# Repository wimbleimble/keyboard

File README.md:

# keebydeeby

I'm sorry I couldn't think of a better name.

Pretty simple, TKL, ISO keyboard with RGB backlighting. Based around an
ATMega32u4, compatible with QMK (and probably a lot more).

## Repo Structure

```
├──📁 enclosure                - Enclosure CAD files.
├──📁 kicad                    - Schematic/PCB CAD file.
│   ├─📁 Custom.pretty         - Custom KiCAD footprints.
│   ├─📁 media                 - Miscellaneous Media Dependencies for PCB.
│   ├─📄 Custom.kicad_sym      - Custom KiCAD symbols.
│   ├─📄 keyboard.kicad_pro    - KiCAD project file.
│   ├─📄 keyboard.kicad_pcb    - PCB File
│   ├─📄 keyboard.kicad_sch    - Master schematic page.
│   ├─📄 key-matrix.kicad_sch  - Key matrix schematic page.
│   ├─📄 LEDS.kicad_sch        - RBG matrix schematic page.
│   ├─📄 mcu.kicad_sch         - Microcontroller schematic page.
│   ├─📄 fp-info-cache         - KiCAD internal file.
│   ├─📄 fp-lib-table          - KiCAD internal file
│   └─📄 sym-lib-table         - KiCAD internal file.
├─📁 plate                     - Plate CAD files.
│   └─📄 plate.svg             - CAD drawing of plate.
└─📄 README.md                 - You're looking at it.
```

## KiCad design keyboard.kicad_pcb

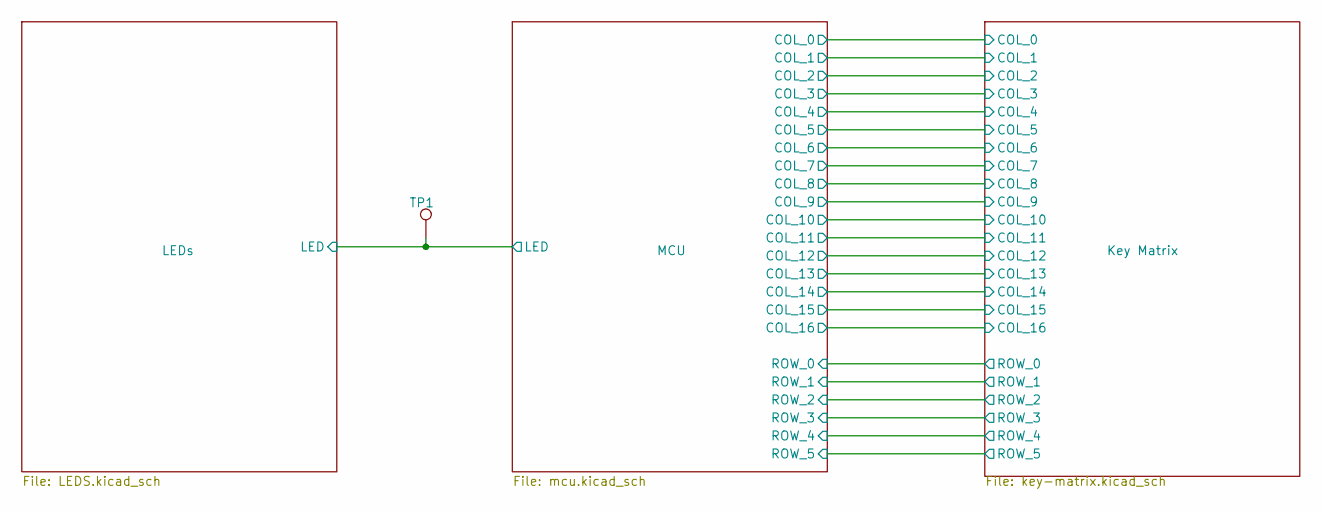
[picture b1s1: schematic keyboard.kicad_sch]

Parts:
TP1: TestPoint; TestPoint_THTPad_D1.0mm_Drill0.5mm

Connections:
/LEDs/LED: TP1.1; also elsewhere on the board

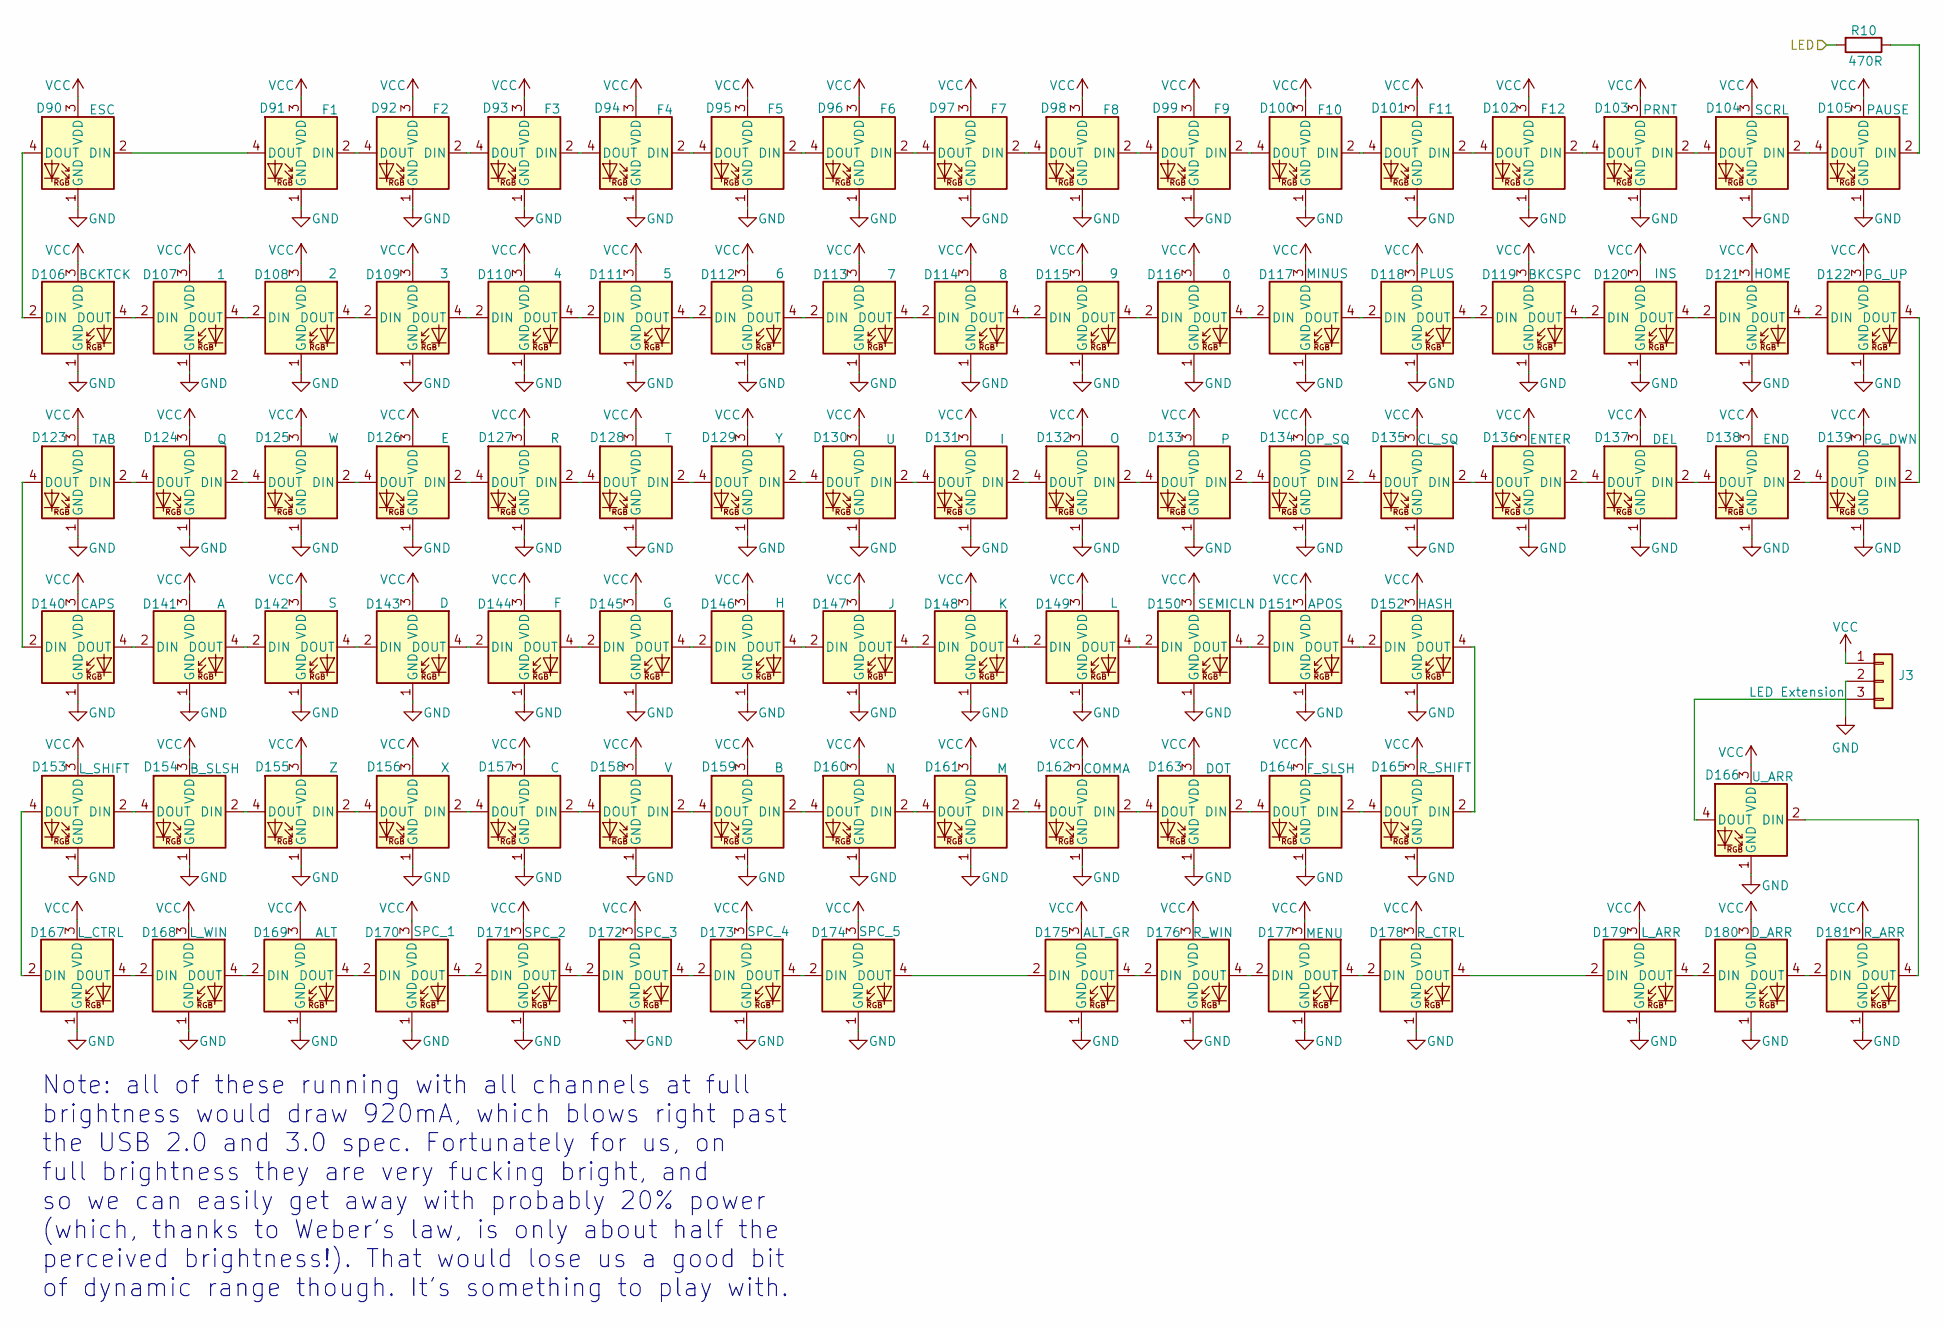
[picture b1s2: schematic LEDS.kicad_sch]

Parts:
D90, D91, D92, D93, D94, D95, D96, D97, D98, D99, D100, D101, D102, D103, D104, D105, D106, D107, D108, D109, D110, D111, D112, D113, D114, D115, D116, D117, D118, D119, D120, D121, D122, D123, D124, D125, D126, D127, D128, D129, D130, D131, D132, D133, D134, D135, D136, D137, D138, D139, D140, D141, D142, D143, D144, D145, D146, D147, D148, D149, D150, D151, D152, D153, D154, D155, D156, D157, D158, D159, D160, D161, D162, D163, D164, D165, D166, D167, D168, D169, D170, D171, D172, D173, D174, D175, D176, D177, D178, D179, D180, D181: SK6803MINI-E; SK6803MINI-E_Bottom_Up
J3: LED Extension; PinHeader_1x03_P2.54mm_Horizontal
R10: 470R; R_0603_1608Metric_Pad0.98x0.95mm_HandSolder

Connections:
/LEDs/LED: R10.2; also elsewhere on the board
GND: D90.1 (GND), D91.1 (GND), D92.1 (GND), D93.1 (GND), D94.1 (GND), D95.1 (GND), D96.1 (GND), D97.1 (GND), D98.1 (GND), D99.1 (GND), D100.1 (GND), D101.1 (GND), D102.1 (GND), D103.1 (GND), D104.1 (GND), D105.1 (GND), D106.1 (GND), D107.1 (GND), D108.1 (GND), D109.1 (GND), D110.1 (GND), D111.1 (GND), D112.1 (GND), D113.1 (GND), D114.1 (GND), D115.1 (GND), D116.1 (GND), D117.1 (GND), D118.1 (GND), D119.1 (GND), D120.1 (GND), D121.1 (GND), D122.1 (GND), D123.1 (GND), D124.1 (GND), D125.1 (GND), D126.1 (GND), D127.1 (GND), D128.1 (GND), D129.1 (GND), D130.1 (GND), D131.1 (GND), D132.1 (GND), D133.1 (GND), D134.1 (GND), D135.1 (GND), D136.1 (GND), D137.1 (GND), D138.1 (GND), D139.1 (GND), D140.1 (GND), D141.1 (GND), D142.1 (GND), D143.1 (GND), D144.1 (GND), D145.1 (GND), D146.1 (GND), D147.1 (GND), D148.1 (GND), D149.1 (GND), D150.1 (GND), D151.1 (GND), D152.1 (GND), D153.1 (GND), D154.1 (GND), D155.1 (GND), D156.1 (GND), D157.1 (GND), D158.1 (GND), D159.1 (GND), D160.1 (GND), D161.1 (GND), D162.1 (GND), D163.1 (GND), D164.1 (GND), D165.1 (GND), D166.1 (GND), D167.1 (GND), D168.1 (GND), D169.1 (GND), D170.1 (GND), D171.1 (GND), D172.1 (GND), D173.1 (GND), D174.1 (GND), D175.1 (GND), D176.1 (GND), D177.1 (GND), D178.1 (GND), D179.1 (GND), D180.1 (GND), D181.1 (GND), J3.2; also elsewhere on the board
unnamed: D90.2 (DIN), D91.4 (DOUT)
unnamed: D91.2 (DIN), D92.4 (DOUT)
unnamed: D92.2 (DIN), D93.4 (DOUT)
unnamed: D93.2 (DIN), D94.4 (DOUT)
unnamed: D94.2 (DIN), D95.4 (DOUT)
unnamed: D95.2 (DIN), D96.4 (DOUT)
unnamed: D96.2 (DIN), D97.4 (DOUT)
unnamed: D97.2 (DIN), D98.4 (DOUT)
unnamed: D98.2 (DIN), D99.4 (DOUT)
unnamed: D100.2 (DIN), D101.4 (DOUT)
unnamed: D99.2 (DIN), D100.4 (DOUT)
unnamed: D101.2 (DIN), D102.4 (DOUT)
unnamed: D102.2 (DIN), D103.4 (DOUT)
unnamed: D103.2 (DIN), D104.4 (DOUT)
unnamed: D104.2 (DIN), D105.4 (DOUT)
unnamed: D105.2 (DIN), R10.1
unnamed: D90.4 (DOUT), D106.2 (DIN)
unnamed: D106.4 (DOUT), D107.2 (DIN)
unnamed: D107.4 (DOUT), D108.2 (DIN)
unnamed: D108.4 (DOUT), D109.2 (DIN)
unnamed: D109.4 (DOUT), D110.2 (DIN)
unnamed: D110.4 (DOUT), D111.2 (DIN)
unnamed: D111.4 (DOUT), D112.2 (DIN)
unnamed: D112.4 (DOUT), D113.2 (DIN)
unnamed: D113.4 (DOUT), D114.2 (DIN)
unnamed: D114.4 (DOUT), D115.2 (DIN)
unnamed: D115.4 (DOUT), D116.2 (DIN)
unnamed: D116.4 (DOUT), D117.2 (DIN)
unnamed: D117.4 (DOUT), D118.2 (DIN)
unnamed: D118.4 (DOUT), D119.2 (DIN)
unnamed: D119.4 (DOUT), D120.2 (DIN)
unnamed: D120.4 (DOUT), D121.2 (DIN)
unnamed: D121.4 (DOUT), D122.2 (DIN)
unnamed: D122.4 (DOUT), D139.2 (DIN)
unnamed: D123.2 (DIN), D124.4 (DOUT)
unnamed: D123.4 (DOUT), D140.2 (DIN)
unnamed: D124.2 (DIN), D125.4 (DOUT)
unnamed: D125.2 (DIN), D126.4 (DOUT)
unnamed: D126.2 (DIN), D127.4 (DOUT)
unnamed: D127.2 (DIN), D128.4 (DOUT)
unnamed: D128.2 (DIN), D129.4 (DOUT)
unnamed: D129.2 (DIN), D130.4 (DOUT)
unnamed: D130.2 (DIN), D131.4 (DOUT)
unnamed: D131.2 (DIN), D132.4 (DOUT)
unnamed: D132.2 (DIN), D133.4 (DOUT)
unnamed: D133.2 (DIN), D134.4 (DOUT)
unnamed: D134.2 (DIN), D135.4 (DOUT)
unnamed: D135.2 (DIN), D136.4 (DOUT)
unnamed: D136.2 (DIN), D137.4 (DOUT)
unnamed: D137.2 (DIN), D138.4 (DOUT)
unnamed: D138.2 (DIN), D139.4 (DOUT)
unnamed: D140.4 (DOUT), D141.2 (DIN)
unnamed: D141.4 (DOUT), D142.2 (DIN)
unnamed: D142.4 (DOUT), D143.2 (DIN)
unnamed: D143.4 (DOUT), D144.2 (DIN)
unnamed: D144.4 (DOUT), D145.2 (DIN)
unnamed: D145.4 (DOUT), D146.2 (DIN)
unnamed: D146.4 (DOUT), D147.2 (DIN)
unnamed: D147.4 (DOUT), D148.2 (DIN)
unnamed: D148.4 (DOUT), D149.2 (DIN)
unnamed: D149.4 (DOUT), D150.2 (DIN)
unnamed: D150.4 (DOUT), D151.2 (DIN)
unnamed: D151.4 (DOUT), D152.2 (DIN)
unnamed: D152.4 (DOUT), D165.2 (DIN)
unnamed: D153.2 (DIN), D154.4 (DOUT)
unnamed: D153.4 (DOUT), D167.2 (DIN)
unnamed: D154.2 (DIN), D155.4 (DOUT)
unnamed: D155.2 (DIN), D156.4 (DOUT)
unnamed: D156.2 (DIN), D157.4 (DOUT)
unnamed: D157.2 (DIN), D158.4 (DOUT)
unnamed: D158.2 (DIN), D159.4 (DOUT)
unnamed: D159.2 (DIN), D160.4 (DOUT)
unnamed: D160.2 (DIN), D161.4 (DOUT)
unnamed: D161.2 (DIN), D162.4 (DOUT)
unnamed: D162.2 (DIN), D163.4 (DOUT)
unnamed: D163.2 (DIN), D164.4 (DOUT)
unnamed: D164.2 (DIN), D165.4 (DOUT)
unnamed: D166.2 (DIN), D181.4 (DOUT)
unnamed: D166.4 (DOUT), J3.3
unnamed: D167.4 (DOUT), D168.2 (DIN)
unnamed: D168.4 (DOUT), D169.2 (DIN)
unnamed: D169.4 (DOUT), D170.2 (DIN)
unnamed: D170.4 (DOUT), D171.2 (DIN)
unnamed: D171.4 (DOUT), D172.2 (DIN)
unnamed: D172.4 (DOUT), D173.2 (DIN)
unnamed: D173.4 (DOUT), D174.2 (DIN)
unnamed: D174.4 (DOUT), D175.2 (DIN)
unnamed: D175.4 (DOUT), D176.2 (DIN)
unnamed: D176.4 (DOUT), D177.2 (DIN)
unnamed: D177.4 (DOUT), D178.2 (DIN)
unnamed: D178.4 (DOUT), D179.2 (DIN)
unnamed: D179.4 (DOUT), D180.2 (DIN)
unnamed: D180.4 (DOUT), D181.2 (DIN)
VCC: D90.3 (VDD), D91.3 (VDD), D92.3 (VDD), D93.3 (VDD), D94.3 (VDD), D95.3 (VDD), D96.3 (VDD), D97.3 (VDD), D98.3 (VDD), D99.3 (VDD), D100.3 (VDD), D101.3 (VDD), D102.3 (VDD), D103.3 (VDD), D104.3 (VDD), D105.3 (VDD), D106.3 (VDD), D107.3 (VDD), D108.3 (VDD), D109.3 (VDD), D110.3 (VDD), D111.3 (VDD), D112.3 (VDD), D113.3 (VDD), D114.3 (VDD), D115.3 (VDD), D116.3 (VDD), D117.3 (VDD), D118.3 (VDD), D119.3 (VDD), D120.3 (VDD), D121.3 (VDD), D122.3 (VDD), D123.3 (VDD), D124.3 (VDD), D125.3 (VDD), D126.3 (VDD), D127.3 (VDD), D128.3 (VDD), D129.3 (VDD), D130.3 (VDD), D131.3 (VDD), D132.3 (VDD), D133.3 (VDD), D134.3 (VDD), D135.3 (VDD), D136.3 (VDD), D137.3 (VDD), D138.3 (VDD), D139.3 (VDD), D140.3 (VDD), D141.3 (VDD), D142.3 (VDD), D143.3 (VDD), D144.3 (VDD), D145.3 (VDD), D146.3 (VDD), D147.3 (VDD), D148.3 (VDD), D149.3 (VDD), D150.3 (VDD), D151.3 (VDD), D152.3 (VDD), D153.3 (VDD), D154.3 (VDD), D155.3 (VDD), D156.3 (VDD), D157.3 (VDD), D158.3 (VDD), D159.3 (VDD), D160.3 (VDD), D161.3 (VDD), D162.3 (VDD), D163.3 (VDD), D164.3 (VDD), D165.3 (VDD), D166.3 (VDD), D167.3 (VDD), D168.3 (VDD), D169.3 (VDD), D170.3 (VDD), D171.3 (VDD), D172.3 (VDD), D173.3 (VDD), D174.3 (VDD), D175.3 (VDD), D176.3 (VDD), D177.3 (VDD), D178.3 (VDD), D179.3 (VDD), D180.3 (VDD), D181.3 (VDD), J3.1; also elsewhere on the board

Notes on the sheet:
Note: all of these running with all channels at full brightness would draw 920mA, which blows right past the USB 2.0 and 3.0 spec. Fortunately for us, on full brightness they are very fucking bright, and so we can easily get away with probably 20% power (which, thanks to Weber's law, is only about 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

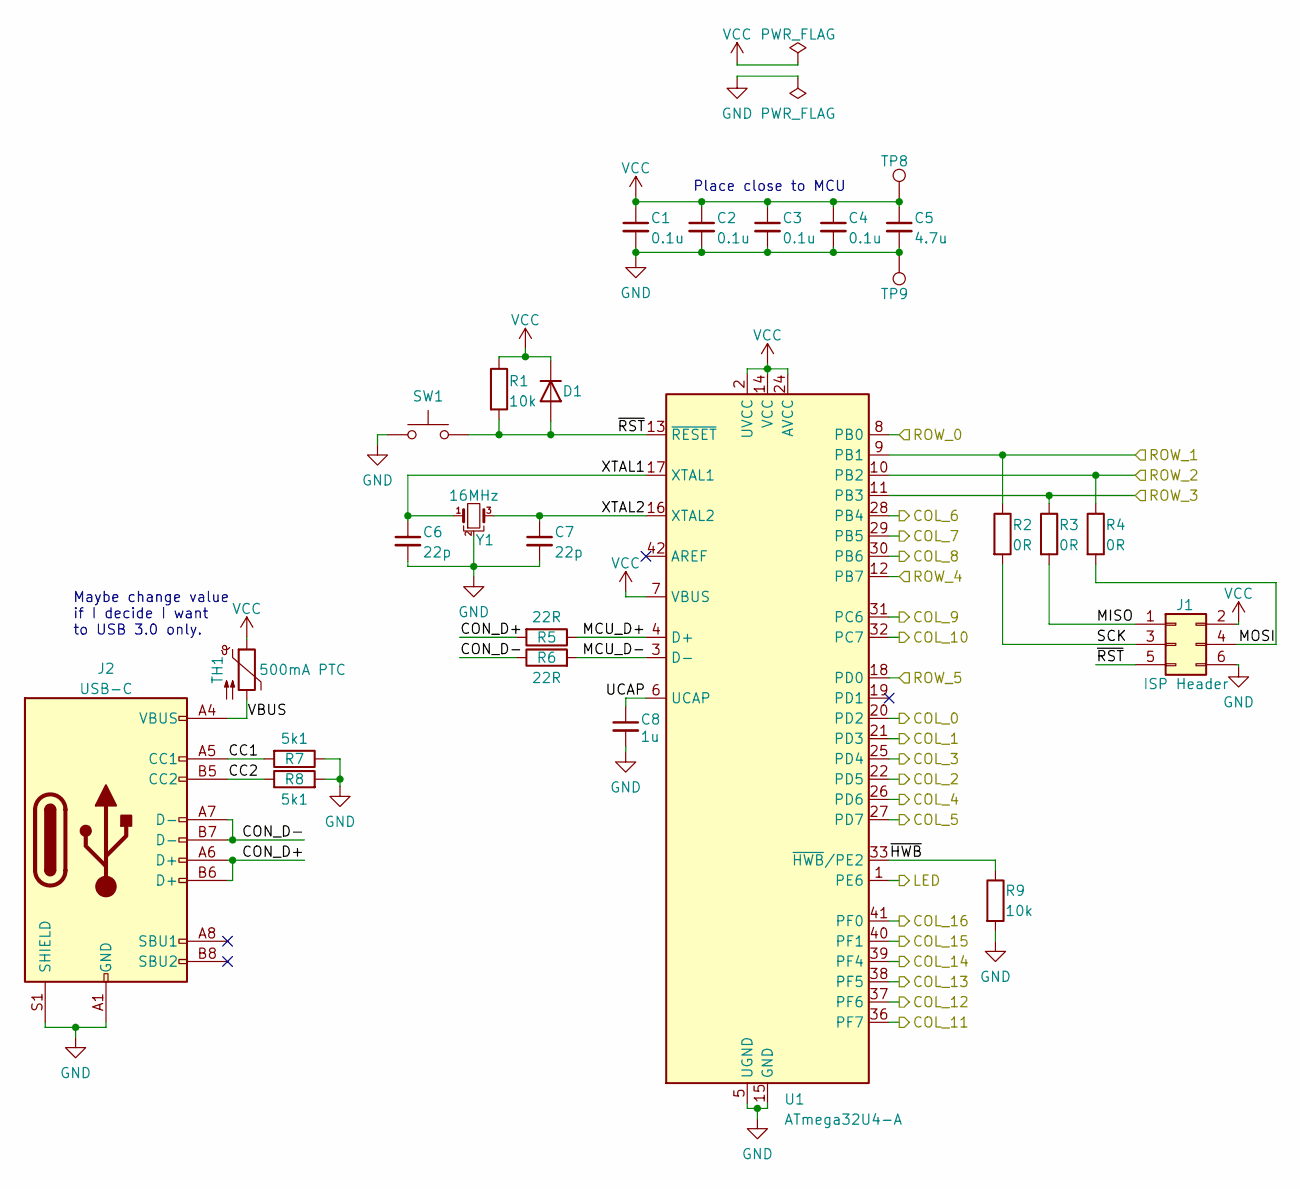
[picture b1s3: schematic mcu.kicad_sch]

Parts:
C1, C2, C3, C4: 0.1u; C_0603_1608Metric_Pad1.08x0.95mm_HandSolder
C5: 4.7u; C_0603_1608Metric_Pad1.08x0.95mm_HandSolder
C6, C7: 22p; C_0603_1608Metric_Pad1.08x0.95mm_HandSolder
C8: 1u; C_0603_1608Metric_Pad1.08x0.95mm_HandSolder
D1: 1N4148; D_SOD-123
J1: ISP Header; PinHeader_2x03_P2.54mm_Vertical
J2: USB-C; USB_C_Receptacle_XKB_U262-16XN-4BVC11
R1, R9: 10k; R_0603_1608Metric_Pad0.98x0.95mm_HandSolder
R2, R3, R4: 0R; R_0603_1608Metric_Pad0.98x0.95mm_HandSolder
R5, R6: 22R; R_0603_1608Metric_Pad0.98x0.95mm_HandSolder
R7, R8: 5k1; R_0603_1608Metric_Pad0.98x0.95mm_HandSolder
SW1: SW_Push; SW_Push_1P1T_NO_6x6mm_H9.5mm
TH1: 500mA PTC; R_1206_3216Metric_Pad1.30x1.75mm_HandSolder
TP8, TP9: TestPoint; TestPoint_THTPad_D1.0mm_Drill0.5mm
U1: ATmega32U4-A; TQFP-44_10x10mm_P0.8mm
Y1: 16MHz; Crystal_SMD_3225-4Pin_3.2x2.5mm_HandSoldering

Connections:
/Key Matrix/COL_0: U1.20 (PD2); also elsewhere on the board
/Key Matrix/COL_1: U1.21 (PD3); also elsewhere on the board
/Key Matrix/COL_2: U1.22 (PD5); also elsewhere on the board
/Key Matrix/COL_3: U1.25 (PD4); also elsewhere on the board
/Key Matrix/COL_4: U1.26 (PD6); also elsewhere on the board
/Key Matrix/COL_5: U1.27 (PD7); also elsewhere on the board
/Key Matrix/COL_6: U1.28 (PB4); also elsewhere on the board
/Key Matrix/COL_7: U1.29 (PB5); also elsewhere on the board
/Key Matrix/COL_8: U1.30 (PB6); also elsewhere on the board
/Key Matrix/COL_9: U1.31 (PC6); also elsewhere on the board
/Key Matrix/COL_10: U1.32 (PC7); also elsewhere on the board
/Key Matrix/COL_11: U1.36 (PF7); also elsewhere on the board
/Key Matrix/COL_12: U1.37 (PF6); also elsewhere on the board
/Key Matrix/COL_13: U1.38 (PF5); also elsewhere on the board
/Key Matrix/COL_14: U1.39 (PF4); also elsewhere on the board
/Key Matrix/COL_15: U1.40 (PF1); also elsewhere on the board
/Key Matrix/COL_16: U1.41 (PF0); also elsewhere on the board
/Key Matrix/ROW_0: U1.8 (PB0); also elsewhere on the board
/Key Matrix/ROW_1: R2.1, U1.9 (PB1); also elsewhere on the board
/Key Matrix/ROW_2: R4.1, U1.10 (PB2); also elsewhere on the board
/Key Matrix/ROW_3: R3.1, U1.11 (PB3); also elsewhere on the board
/Key Matrix/ROW_4: U1.12 (PB7); also elsewhere on the board
/Key Matrix/ROW_5: U1.18 (PD0); also elsewhere on the board
/LEDs/LED: U1.1 (PE6); also elsewhere on the board
/MCU/CC1: J2.A5 (CC1), R7.2
/MCU/CC2: J2.B5 (CC2), R8.1
/MCU/CON_D+: J2.A6 (D+), J2.B6 (D+), R5.2
/MCU/CON_D-: J2.A7 (D-), J2.B7 (D-), R6.1
/MCU/MCU_D+: R5.1, U1.4 (D+)
/MCU/MCU_D-: R6.2, U1.3 (D-)
/MCU/MISO: J1.1, R3.2
/MCU/MOSI: J1.4, R4.2
/MCU/SCK: J1.3, R2.2
/MCU/UCAP: C8.1, U1.6 (UCAP)
/MCU/VBUS: J2.A4 (VBUS), J2.A9 (VBUS), J2.B4 (VBUS), J2.B9 (VBUS), TH1.2
/MCU/XTAL1: C6.1, U1.17 (XTAL1), Y1.1
/MCU/XTAL2: C7.1, U1.16 (XTAL2), Y1.3
/MCU/~HWB: R9.1, U1.33 (~HWB/PE2)
/MCU/~RST: D1.2 (A), J1.5, R1.2, SW1.2, U1.13 (~RESET)
GND: C1.2, C2.2, C3.2, C4.2, C5.2, C6.2, C7.2, C8.2, J1.6, J2.A1 (GND), J2.A12 (GND), J2.B1 (GND), J2.B12 (GND), J2.S1 (SHIELD), R7.1, R8.2, R9.2, SW1.1, TP9.1, U1.5 (UGND), U1.15 (GND), U1.23 (GND), U1.35 (GND), U1.43 (GND), Y1.2; also elsewhere on the board
VCC: C1.1, C2.1, C3.1, C4.1, C5.1, D1.1 (K), J1.2, R1.1, TH1.1, TP8.1, U1.2 (UVCC), U1.7 (VBUS), U1.14 (VCC), U1.24 (AVCC), U1.34 (VCC), U1.44 (AVCC); also elsewhere on the board

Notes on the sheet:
Maybe change value if I decide I want to USB 3.0 only.
Place close to MCU

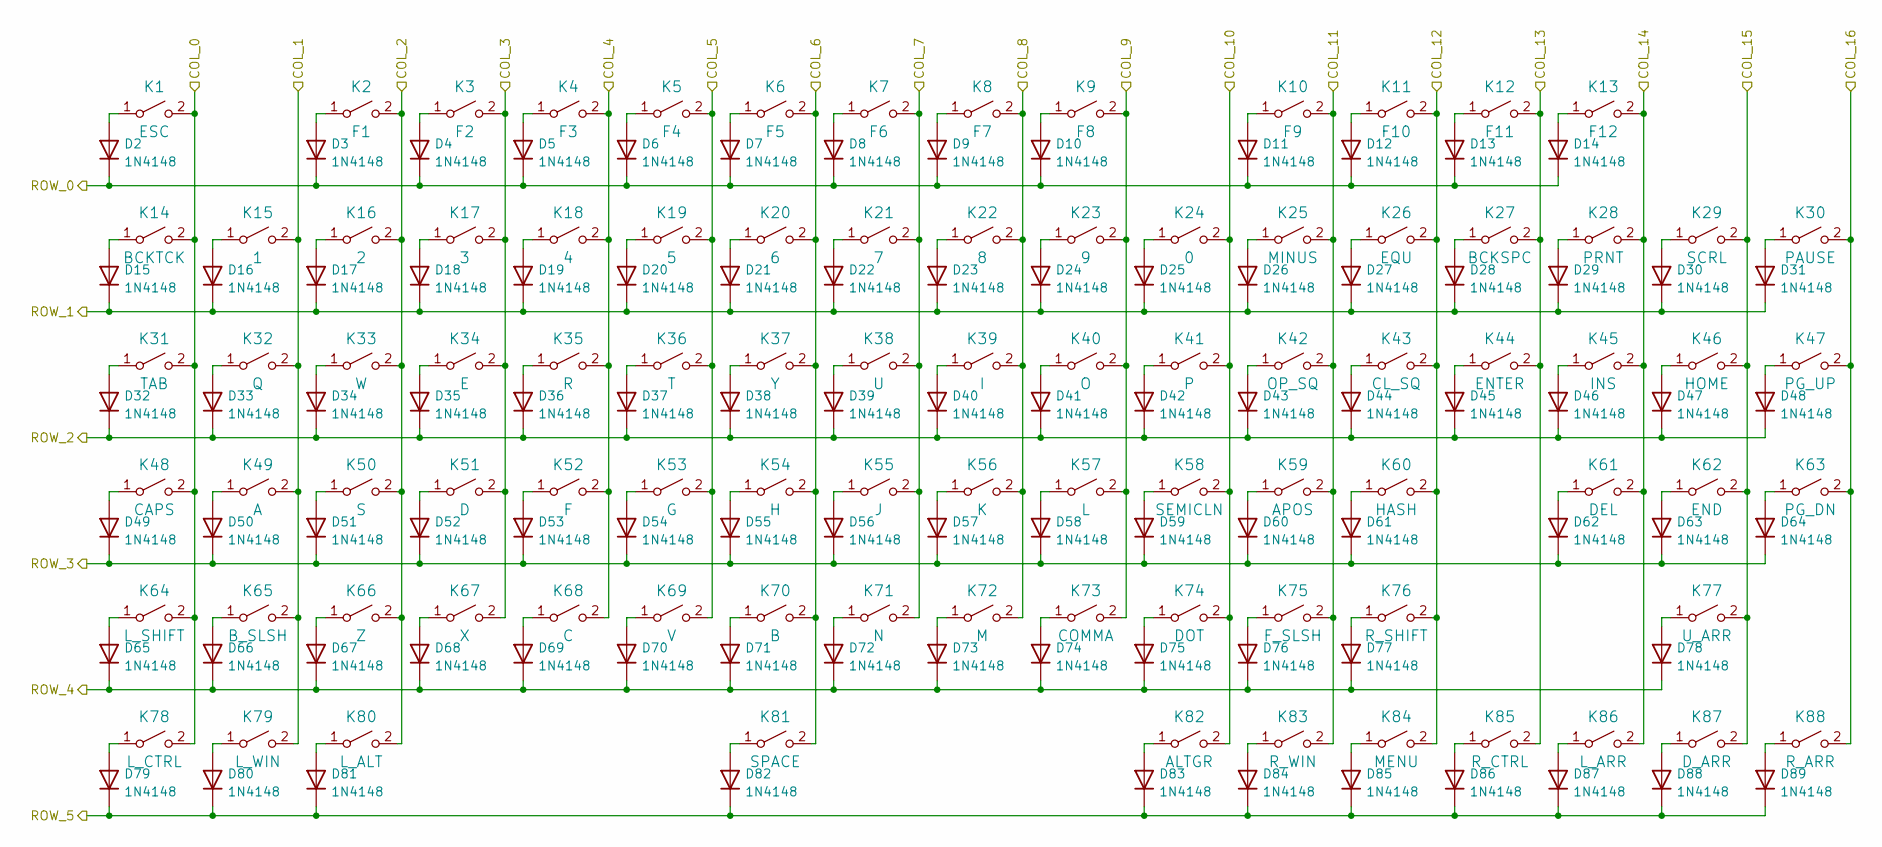
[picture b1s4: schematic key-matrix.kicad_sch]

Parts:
D2, D3, D4, D5, D6, D7, D8, D9, D10, D11, D12, D13, D14, D15, D16, D17, D18, D19, D20, D21, D22, D23, D24, D25, D26, D27, D28, D29, D30, D31, D32, D33, D34, D35, D36, D37, D38, D39, D40, D41, D42, D43, D44, D45, D46, D47, D48, D49, D50, D51, D52, D53, D54, D55, D56, D57, D58, D59, D60, D61, D62, D63, D64, D65, D66, D67, D68, D69, D70, D71, D72, D73, D74, D75, D76, D77, D78, D79, D80, D81, D82, D83, D84, D85, D86, D87, D88, D89: 1N4148; D_SOD-123
K1: ESC; SW_Cherry_MX_1.00u_PCB
K2: F1; SW_Cherry_MX_1.00u_PCB
K3: F2; SW_Cherry_MX_1.00u_PCB
K4: F3; SW_Cherry_MX_1.00u_PCB
K5: F4; SW_Cherry_MX_1.00u_PCB
K6: F5; SW_Cherry_MX_1.00u_PCB
K7: F6; SW_Cherry_MX_1.00u_PCB
K8: F7; SW_Cherry_MX_1.00u_PCB
K9: F8; SW_Cherry_MX_1.00u_PCB
K10: F9; SW_Cherry_MX_1.00u_PCB
K11: F10; SW_Cherry_MX_1.00u_PCB
K12: F11; SW_Cherry_MX_1.00u_PCB
K13: F12; SW_Cherry_MX_1.00u_PCB
K14: BCKTCK; SW_Cherry_MX_1.00u_PCB
K15: 1; SW_Cherry_MX_1.00u_PCB
K16: 2; SW_Cherry_MX_1.00u_PCB
K17: 3; SW_Cherry_MX_1.00u_PCB
K18: 4; SW_Cherry_MX_1.00u_PCB
K19: 5; SW_Cherry_MX_1.00u_PCB
K20: 6; SW_Cherry_MX_1.00u_PCB
K21: 7; SW_Cherry_MX_1.00u_PCB
K22: 8; SW_Cherry_MX_1.00u_PCB
K23: 9; SW_Cherry_MX_1.00u_PCB
K24: 0; SW_Cherry_MX_1.00u_PCB
K25: MINUS; SW_Cherry_MX_1.00u_PCB
K26: EQU; SW_Cherry_MX_1.00u_PCB
K27: BCKSPC; SW_Cherry_MX_1.00u_PCB
K28: PRNT; SW_Cherry_MX_1.00u_PCB
K29: SCRL; SW_Cherry_MX_1.00u_PCB
K30: PAUSE; SW_Cherry_MX_1.00u_PCB
K31: TAB; SW_Cherry_MX_1.00u_PCB
K32: Q; SW_Cherry_MX_1.00u_PCB
K33: W; SW_Cherry_MX_1.00u_PCB
K34: E; SW_Cherry_MX_1.00u_PCB
K35: R; SW_Cherry_MX_1.00u_PCB
K36: T; SW_Cherry_MX_1.00u_PCB
K37: Y; SW_Cherry_MX_1.00u_PCB
K38: U; SW_Cherry_MX_1.00u_PCB
K39: I; SW_Cherry_MX_1.00u_PCB
K40: O; SW_Cherry_MX_1.00u_PCB
K41: P; SW_Cherry_MX_1.00u_PCB
K42: OP_SQ; SW_Cherry_MX_1.00u_PCB
K43: CL_SQ; SW_Cherry_MX_1.00u_PCB
K44: ENTER; SW_Cherry_MX_1.00u_PCB
K45: INS; SW_Cherry_MX_1.00u_PCB
K46: HOME; SW_Cherry_MX_1.00u_PCB
K47: PG_UP; SW_Cherry_MX_1.00u_PCB
K48: CAPS; SW_Cherry_MX_1.00u_PCB
K49: A; SW_Cherry_MX_1.00u_PCB
K50: S; SW_Cherry_MX_1.00u_PCB
K51: D; SW_Cherry_MX_1.00u_PCB
K52: F; SW_Cherry_MX_1.00u_PCB
K53: G; SW_Cherry_MX_1.00u_PCB
K54: H; SW_Cherry_MX_1.00u_PCB
K55: J; SW_Cherry_MX_1.00u_PCB
K56: K; SW_Cherry_MX_1.00u_PCB
K57: L; SW_Cherry_MX_1.00u_PCB
K58: SEMICLN; SW_Cherry_MX_1.00u_PCB
K59: APOS; SW_Cherry_MX_1.00u_PCB
K60: HASH; SW_Cherry_MX_1.00u_PCB
K61: DEL; SW_Cherry_MX_1.00u_PCB
K62: END; SW_Cherry_MX_1.00u_PCB
K63: PG_DN; SW_Cherry_MX_1.00u_PCB
K64: L_SHIFT; SW_Cherry_MX_1.00u_PCB
K65: B_SLSH; SW_Cherry_MX_1.00u_PCB
K66: Z; SW_Cherry_MX_1.00u_PCB
K67: X; SW_Cherry_MX_1.00u_PCB
K68: C; SW_Cherry_MX_1.00u_PCB
K69: V; SW_Cherry_MX_1.00u_PCB
K70: B; SW_Cherry_MX_1.00u_PCB
K71: N; SW_Cherry_MX_1.00u_PCB
K72: M; SW_Cherry_MX_1.00u_PCB
K73: COMMA; SW_Cherry_MX_1.00u_PCB
K74: DOT; SW_Cherry_MX_1.00u_PCB
K75: F_SLSH; SW_Cherry_MX_1.00u_PCB
K76: R_SHIFT; SW_Cherry_MX_1.00u_PCB
K77: U_ARR; SW_Cherry_MX_1.00u_PCB
K78: L_CTRL; SW_Cherry_MX_1.00u_PCB
K79: L_WIN; SW_Cherry_MX_1.00u_PCB
K80: L_ALT; SW_Cherry_MX_1.00u_PCB
K81: SPACE; SW_Cherry_MX_1.00u_PCB
K82: ALTGR; SW_Cherry_MX_1.00u_PCB
K83: R_WIN; SW_Cherry_MX_1.00u_PCB
K84: MENU; SW_Cherry_MX_1.00u_PCB
K85: R_CTRL; SW_Cherry_MX_1.00u_PCB
K86: L_ARR; SW_Cherry_MX_1.00u_PCB
K87: D_ARR; SW_Cherry_MX_1.00u_PCB
K88: R_ARR; SW_Cherry_MX_1.00u_PCB

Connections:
/Key Matrix/COL_0: K1.2 (B), K14.2 (B), K31.2 (B), K48.2 (B), K64.2 (B), K78.2 (B); also elsewhere on the board
/Key Matrix/COL_1: K15.2 (B), K32.2 (B), K49.2 (B), K65.2 (B), K79.2 (B); also elsewhere on the board
/Key Matrix/COL_2: K2.2 (B), K16.2 (B), K33.2 (B), K50.2 (B), K66.2 (B), K80.2 (B); also elsewhere on the board
/Key Matrix/COL_3: K3.2 (B), K17.2 (B), K34.2 (B), K51.2 (B), K67.2 (B); also elsewhere on the board
/Key Matrix/COL_4: K4.2 (B), K18.2 (B), K35.2 (B), K52.2 (B), K68.2 (B); also elsewhere on the board
/Key Matrix/COL_5: K5.2 (B), K19.2 (B), K36.2 (B), K53.2 (B), K69.2 (B); also elsewhere on the board
/Key Matrix/COL_6: K6.2 (B), K20.2 (B), K37.2 (B), K54.2 (B), K70.2 (B), K81.2 (B); also elsewhere on the board
/Key Matrix/COL_7: K7.2 (B), K21.2 (B), K38.2 (B), K55.2 (B), K71.2 (B); also elsewhere on the board
/Key Matrix/COL_8: K8.2 (B), K22.2 (B), K39.2 (B), K56.2 (B), K72.2 (B); also elsewhere on the board
/Key Matrix/COL_9: K9.2 (B), K23.2 (B), K40.2 (B), K57.2 (B), K73.2 (B); also elsewhere on the board
/Key Matrix/COL_10: K24.2 (B), K41.2 (B), K58.2 (B), K74.2 (B), K82.2 (B); also elsewhere on the board
/Key Matrix/COL_11: K10.2 (B), K25.2 (B), K42.2 (B), K59.2 (B), K75.2 (B), K83.2 (B); also elsewhere on the board
/Key Matrix/COL_12: K11.2 (B), K26.2 (B), K43.2 (B), K60.2 (B), K76.2 (B), K84.2 (B); also elsewhere on the board
/Key Matrix/COL_13: K12.2 (B), K27.2 (B), K44.2 (B), K85.2 (B); also elsewhere on the board
/Key Matrix/COL_14: K13.2 (B), K28.2 (B), K45.2 (B), K61.2 (B), K86.2 (B); also elsewhere on the board
/Key Matrix/COL_15: K29.2 (B), K46.2 (B), K62.2 (B), K77.2 (B), K87.2 (B); also elsewhere on the board
/Key Matrix/COL_16: K30.2 (B), K47.2 (B), K63.2 (B), K88.2 (B); also elsewhere on the board
/Key Matrix/ROW_0: D2.1 (K), D3.1 (K), D4.1 (K), D5.1 (K), D6.1 (K), D7.1 (K), D8.1 (K), D9.1 (K), D10.1 (K), D11.1 (K), D12.1 (K), D13.1 (K), D14.1 (K); also elsewhere on the board
/Key Matrix/ROW_1: D15.1 (K), D16.1 (K), D17.1 (K), D18.1 (K), D19.1 (K), D20.1 (K), D21.1 (K), D22.1 (K), D23.1 (K), D24.1 (K), D25.1 (K), D26.1 (K), D27.1 (K), D28.1 (K), D29.1 (K), D30.1 (K), D31.1 (K); also elsewhere on the board
/Key Matrix/ROW_2: D32.1 (K), D33.1 (K), D34.1 (K), D35.1 (K), D36.1 (K), D37.1 (K), D38.1 (K), D39.1 (K), D40.1 (K), D41.1 (K), D42.1 (K), D43.1 (K), D44.1 (K), D45.1 (K), D46.1 (K), D47.1 (K), D48.1 (K); also elsewhere on the board
/Key Matrix/ROW_3: D49.1 (K), D50.1 (K), D51.1 (K), D52.1 (K), D53.1 (K), D54.1 (K), D55.1 (K), D56.1 (K), D57.1 (K), D58.1 (K), D59.1 (K), D60.1 (K), D61.1 (K), D62.1 (K), D63.1 (K), D64.1 (K); also elsewhere on the board
/Key Matrix/ROW_4: D65.1 (K), D66.1 (K), D67.1 (K), D68.1 (K), D69.1 (K), D70.1 (K), D71.1 (K), D72.1 (K), D73.1 (K), D74.1 (K), D75.1 (K), D76.1 (K), D77.1 (K), D78.1 (K); also elsewhere on the board
/Key Matrix/ROW_5: D79.1 (K), D80.1 (K), D81.1 (K), D82.1 (K), D83.1 (K), D84.1 (K), D85.1 (K), D86.1 (K), D87.1 (K), D88.1 (K), D89.1 (K); also elsewhere on the board
unnamed: D2.2 (A), K1.1 (A)
unnamed: D3.2 (A), K2.1 (A)
unnamed: D4.2 (A), K3.1 (A)
unnamed: D5.2 (A), K4.1 (A)
unnamed: D6.2 (A), K5.1 (A)
unnamed: D7.2 (A), K6.1 (A)
unnamed: D8.2 (A), K7.1 (A)
unnamed: D9.2 (A), K8.1 (A)
unnamed: D10.2 (A), K9.1 (A)
unnamed: D11.2 (A), K10.1 (A)
unnamed: D12.2 (A), K11.1 (A)
unnamed: D13.2 (A), K12.1 (A)
unnamed: D14.2 (A), K13.1 (A)
unnamed: D15.2 (A), K14.1 (A)
unnamed: D16.2 (A), K15.1 (A)
unnamed: D17.2 (A), K16.1 (A)
unnamed: D18.2 (A), K17.1 (A)
unnamed: D19.2 (A), K18.1 (A)
unnamed: D20.2 (A), K19.1 (A)
unnamed: D21.2 (A), K20.1 (A)
unnamed: D22.2 (A), K21.1 (A)
unnamed: D23.2 (A), K22.1 (A)
unnamed: D24.2 (A), K23.1 (A)
unnamed: D25.2 (A), K24.1 (A)
unnamed: D26.2 (A), K25.1 (A)
unnamed: D27.2 (A), K26.1 (A)
unnamed: D28.2 (A), K27.1 (A)
unnamed: D29.2 (A), K28.1 (A)
unnamed: D30.2 (A), K29.1 (A)
unnamed: D31.2 (A), K30.1 (A)
unnamed: D32.2 (A), K31.1 (A)
unnamed: D33.2 (A), K32.1 (A)
unnamed: D34.2 (A), K33.1 (A)
unnamed: D35.2 (A), K34.1 (A)
unnamed: D36.2 (A), K35.1 (A)
unnamed: D37.2 (A), K36.1 (A)
unnamed: D38.2 (A), K37.1 (A)
unnamed: D39.2 (A), K38.1 (A)
unnamed: D40.2 (A), K39.1 (A)
unnamed: D41.2 (A), K40.1 (A)
unnamed: D42.2 (A), K41.1 (A)
unnamed: D43.2 (A), K42.1 (A)
unnamed: D44.2 (A), K43.1 (A)
unnamed: D45.2 (A), K44.1 (A)
unnamed: D46.2 (A), K45.1 (A)
unnamed: D47.2 (A), K46.1 (A)
unnamed: D48.2 (A), K47.1 (A)
unnamed: D49.2 (A), K48.1 (A)
unnamed: D50.2 (A), K49.1 (A)
unnamed: D51.2 (A), K50.1 (A)
unnamed: D52.2 (A), K51.1 (A)
unnamed: D53.2 (A), K52.1 (A)
unnamed: D54.2 (A), K53.1 (A)
unnamed: D55.2 (A), K54.1 (A)
unnamed: D56.2 (A), K55.1 (A)
unnamed: D57.2 (A), K56.1 (A)
unnamed: D58.2 (A), K57.1 (A)
unnamed: D59.2 (A), K58.1 (A)
unnamed: D60.2 (A), K59.1 (A)
unnamed: D61.2 (A), K60.1 (A)
unnamed: D62.2 (A), K61.1 (A)
unnamed: D63.2 (A), K62.1 (A)
unnamed: D64.2 (A), K63.1 (A)
unnamed: D65.2 (A), K64.1 (A)
unnamed: D66.2 (A), K65.1 (A)
unnamed: D67.2 (A), K66.1 (A)
unnamed: D68.2 (A), K67.1 (A)
unnamed: D69.2 (A), K68.1 (A)
unnamed: D70.2 (A), K69.1 (A)
unnamed: D71.2 (A), K70.1 (A)
unnamed: D72.2 (A), K71.1 (A)
unnamed: D73.2 (A), K72.1 (A)
unnamed: D74.2 (A), K73.1 (A)
unnamed: D75.2 (A), K74.1 (A)
unnamed: D76.2 (A), K75.1 (A)
unnamed: D77.2 (A), K76.1 (A)
unnamed: D78.2 (A), K77.1 (A)
unnamed: D79.2 (A), K78.1 (A)
unnamed: D80.2 (A), K79.1 (A)
unnamed: D81.2 (A), K80.1 (A)
unnamed: D82.2 (A), K81.1 (A)
unnamed: D83.2 (A), K82.1 (A)
unnamed: D84.2 (A), K83.1 (A)
unnamed: D85.2 (A), K84.1 (A)
unnamed: D86.2 (A), K85.1 (A)
unnamed: D87.2 (A), K86.1 (A)
unnamed: D88.2 (A), K87.1 (A)
unnamed: D89.2 (A), K88.1 (A)

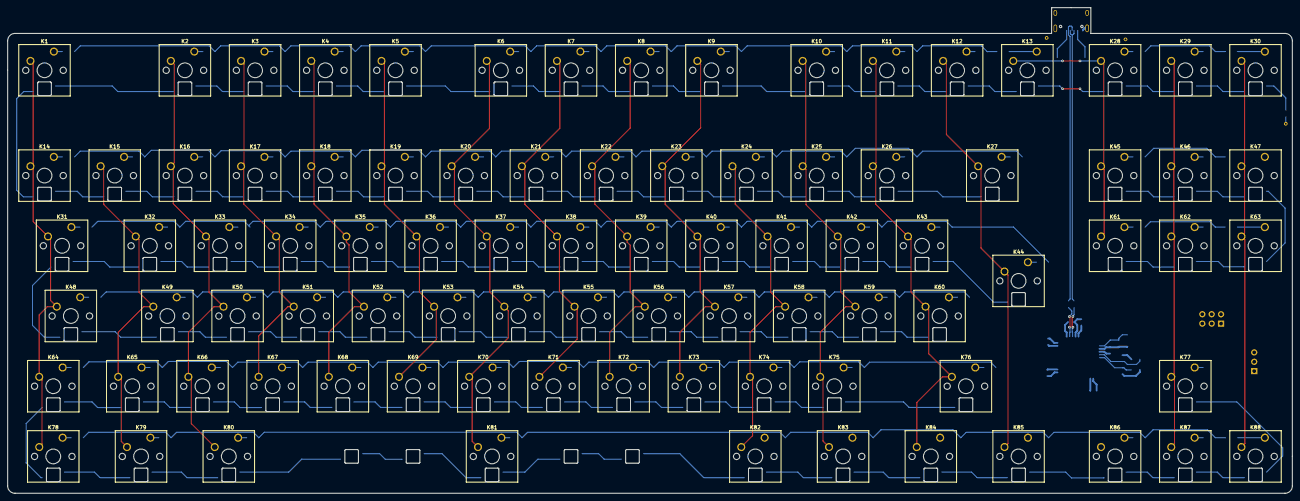
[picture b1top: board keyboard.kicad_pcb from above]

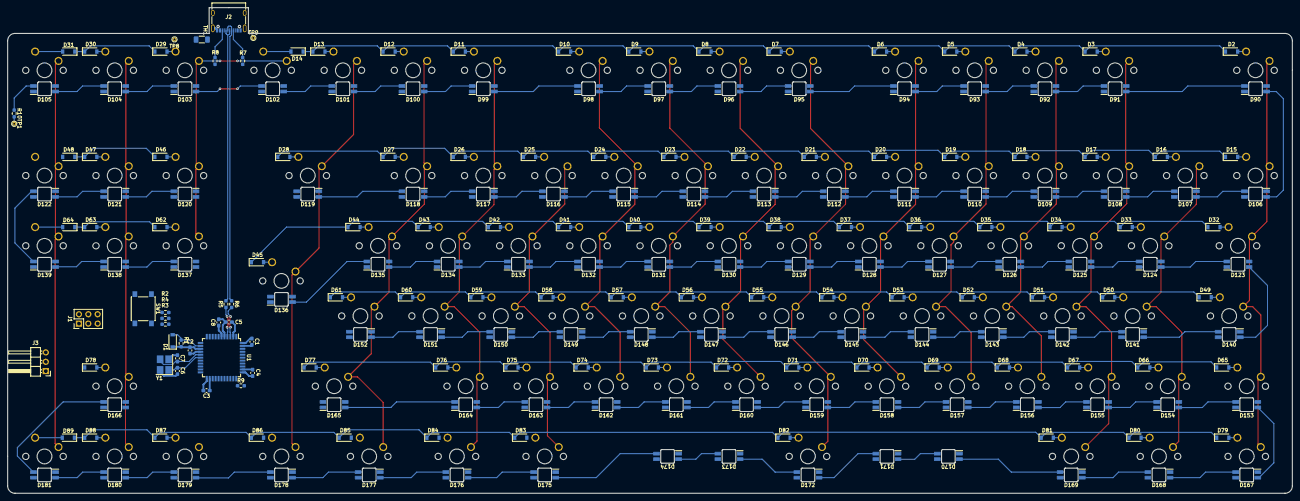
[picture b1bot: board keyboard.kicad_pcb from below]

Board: 2 copper layers, 348.6 x 131.8 mm, 297 parts (209 on the bottom side), 222 nets.

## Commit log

2022-08-14 first draft
2022-08-14 tweaked some bits
2022-08-15 more tweaks
2022-08-17 keyswitch placement
2022-08-17 more layout
2022-08-17 rough layout complete
2022-08-18 before i fuck up
2022-08-18 fucking with pinout
2022-08-19 before i break something
2022-08-19 end of day. NEARLY DONEgit status!
2022-08-20 needs lots of tidying
2022-08-21 viaing
2022-08-23 fixed some of the more bizarre routing decisions
2024-05-28 updated library references to local
2024-06-21 tidying up
2024-06-21 added readme, untracked file
2024-06-21 fixed README
